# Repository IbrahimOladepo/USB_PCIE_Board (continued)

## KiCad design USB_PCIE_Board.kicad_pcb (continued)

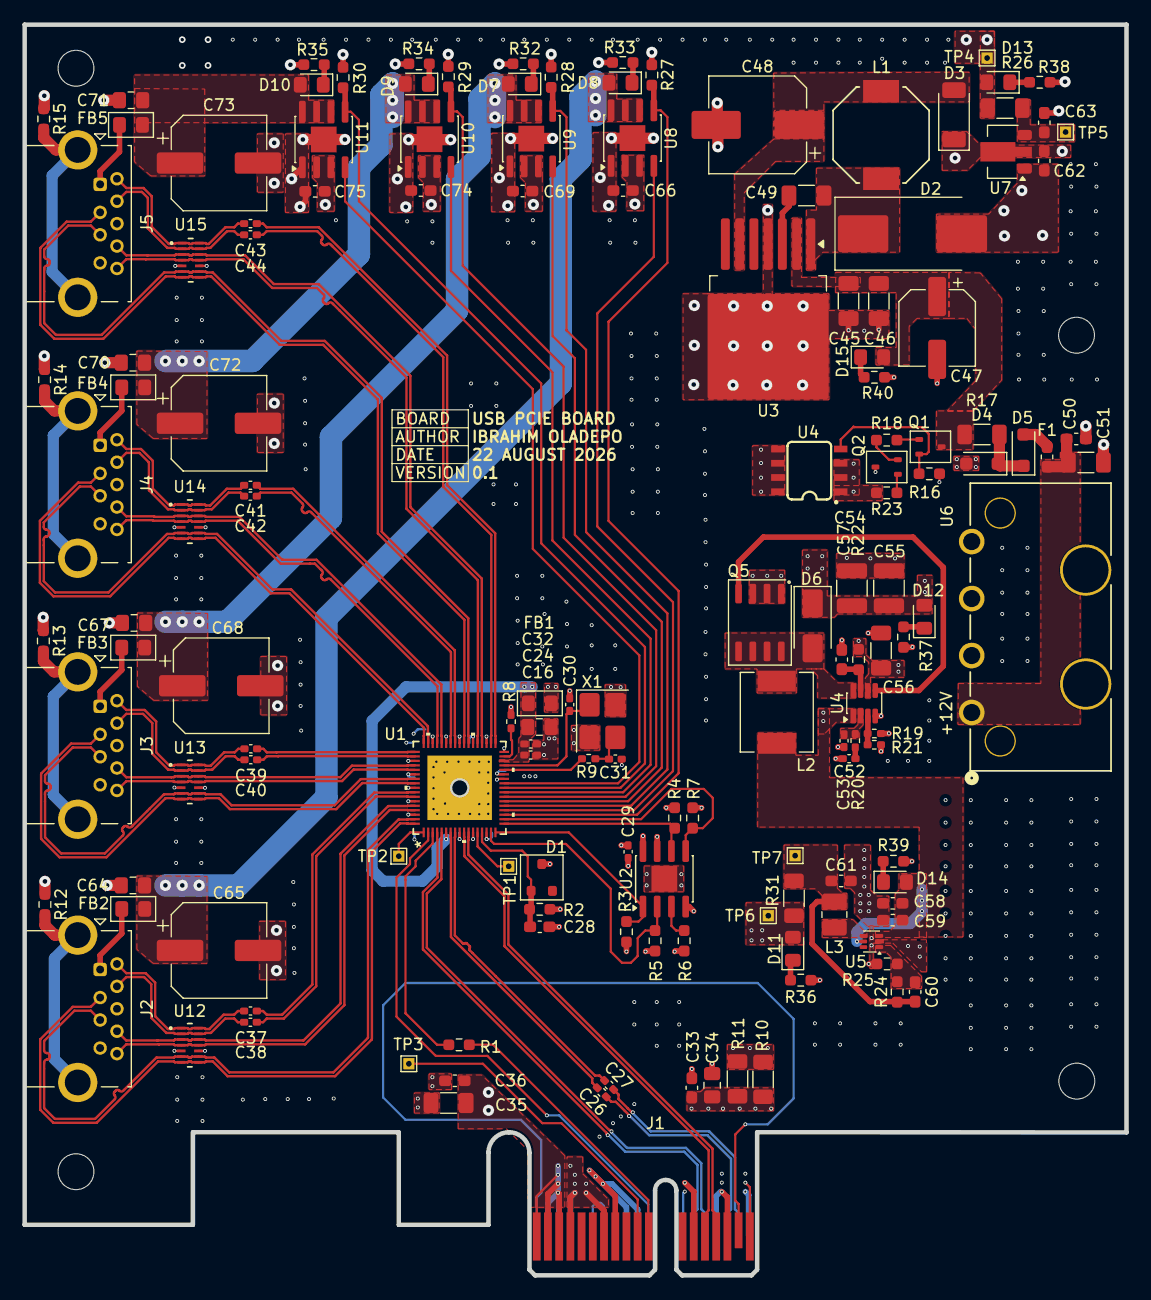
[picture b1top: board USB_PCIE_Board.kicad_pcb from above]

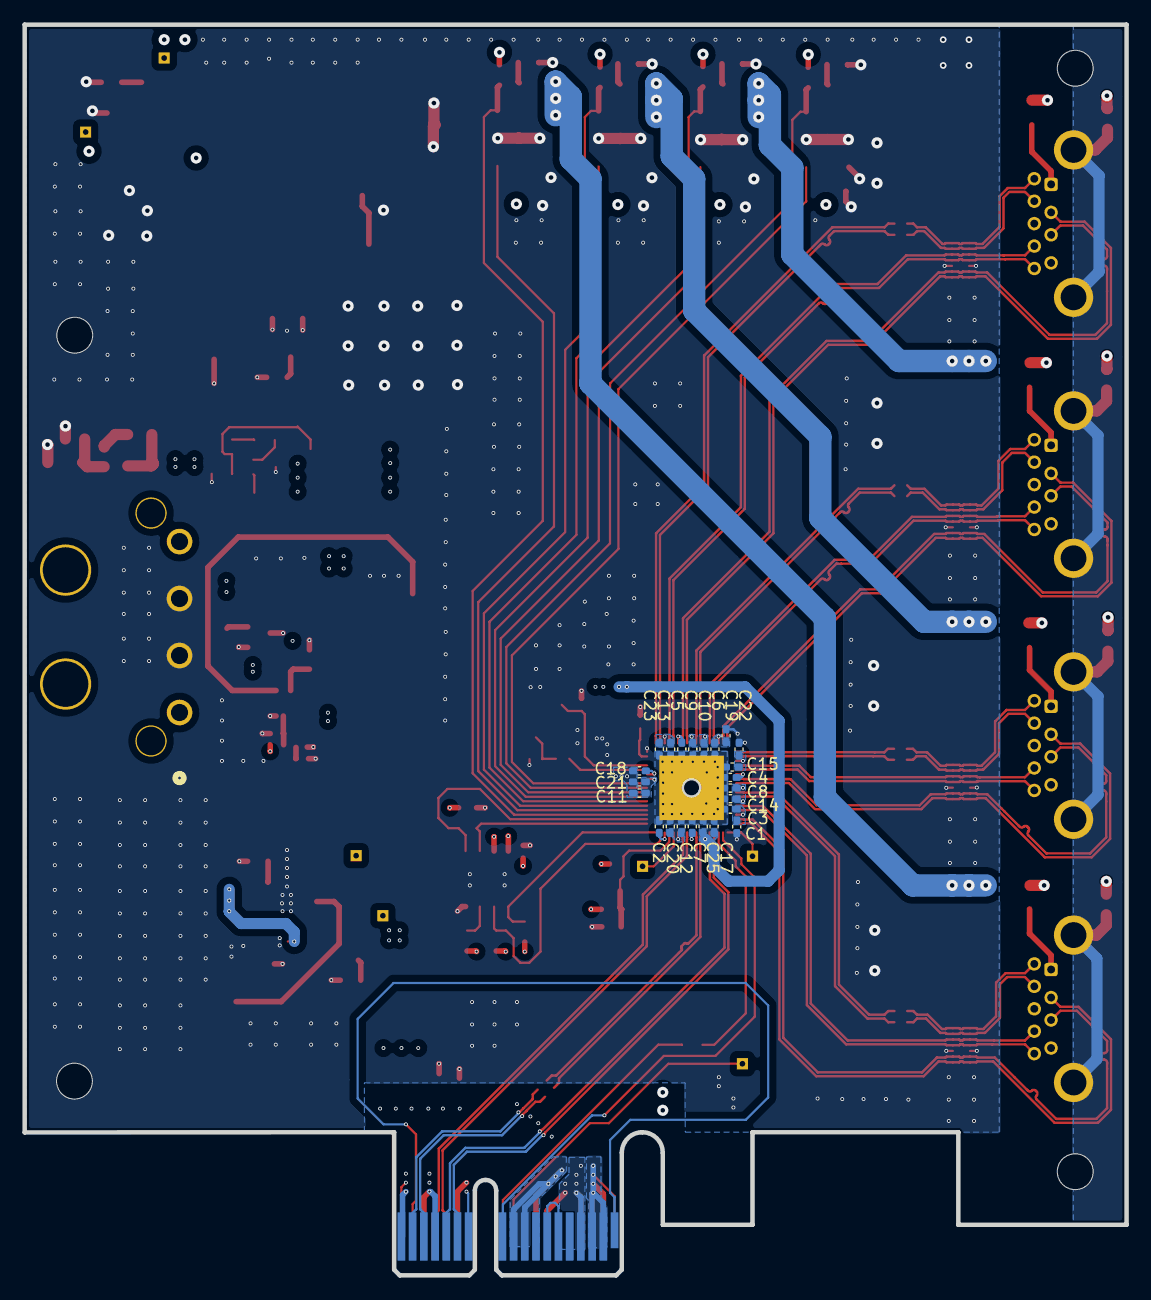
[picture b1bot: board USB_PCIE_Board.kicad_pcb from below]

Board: 4 copper layers, 98.2 x 111.5 mm, 175 parts (23 on the bottom side), 114 nets.

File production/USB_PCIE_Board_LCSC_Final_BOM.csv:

LCSC Part Number,Manufacture Part Number,Manufacturer,Customer NO.,Package,Description,RoHS,Quantity,Unit Price($),Ext.Price($),Estimated lead time (business days),Updated lead time,Date Code / Lot No.
C14663,CC0603KRX7R9BB104,YAGEO,"C33,C36,C50,C57,C59",0603,100nF ±10% 50V Ceramic Capacitor X7R 0603,YES,50,0.0151,0.76,,,
C60474,CC0402KRX7R7BB104,YAGEO,"C18,C19,C20,C21,C22,C23,C24,C25,C26,C27,C29,C37,C38,C39,C40,C41,",0402,100nF ±10% 16V Ceramic Capacitor X7R 0402,YES,100,0.0054,0.54,,,
C18305,BLM21PG600SN1D,muRata,"FB1,FB2,FB3,FB4,FB5",0805,60Ω@100MHz 1 Line Ferrite Bead 0805 3.5A 20mΩ,YES,20,0.0402,0.80,,,
C1972746,SF-0603S315-2,BOURNS,F1,0603,3.15A Surface Mount 0603,YES,2,0.5505,1.10,,,
C5588998,APTD2012LSYCK,Kingbright,"D14,D15",0805,Yellow 590nm LED Indication - Discrete 1.85V 0805,YES,5,0.2268,1.13,,,
C2837824,SMLMN2BCTT86C,ROHM,"D11,D12,D13",0805,Blue 476nm LED Indication - Discrete 2.9V 0805,YES,10,0.3083,3.08,,,
C2992528,SMLMN2WB1CW1,ROHM,"D7,D8,D9,D10",0805,White LED Indication - Discrete 2.9V 0805,YES,10,0.3253,3.25,,,
C110484,B320A-13-F,DIODES,D6,SMA(DO-214AC),1 Independent 20V 500mV@3A 3A SMA(DO-214AC) Single Diodes RoHS,YES,5,0.1615,0.81,,,
C2845139,RBR2MM30BTR,ROHM,"D4,D5",SOD-123FL,Diode Independent 30V 2A Surface Mount SOD-123FL,YES,5,0.1398,0.70,,,
C253526,RSX501LAM20TR,ROHM,D3,SOD-128,Diode 20V 5A Surface Mount SOD-128,YES,5,0.2183,1.09,,,
C85100,B560C-13-F,DIODES,D2,SMC(DO-214AB),1 Independent 60V 700mV@5A 5A SMC(DO-214AB) Single Diodes RoHS,YES,5,0.2117,1.06,,,
C261914,"1SS294,LF",TOSHIBA,D1,SC-59,Diode 40V 100mA Surface Mount SC-59,YES,10,0.0594,0.59,,,
C190722,16SVPC150M,PANASONIC,"C65,C68,C72,C73","SMD,D8xL6.9mm","150uF ±20% 16V Aluminum - Polymer Capacitors SMD,D8xL6.9mm 2000hrs@105℃",YES,8,1.1395,9.12,,,
C77042,GRM188R60J226MEA0D,muRata,"C58,C60,C61",0603,22uF ±20% 6.3V Ceramic Capacitor X5R 0603,YES,10,0.0572,0.57,,,
C60137,CC0402JRNPO9BN470,YAGEO,C53,0402,47pF ±5% 50V Ceramic Capacitor NP0 0402,YES,100,0.0028,0.28,,,
C23742,CL32A107MPVNNNE,Samsung Electro-Mechanics,"C54,C55",1210,100uF ±20% 10V Ceramic Capacitor X5R 1210,YES,4,0.5051,2.02,,,
C108081,RC1206JR-070RL,YAGEO,"R10,R11,R17,R26,R31",1206,0Ω 250mW 200V Thick Film Resistor ±5% 1206 Chip Resistor - Surface Mount RoHS,YES,50,0.0114,0.57,,,
C60133,CC0402KRX7R9BB103,YAGEO,"C1,C2,C3,C4,C5,C6,C7,C8,C9,C10,C11,C12,C13,C14,C15,C16,C17",0402,10nF ±10% 50V Ceramic Capacitor X7R 0402,YES,100,0.0056,0.56,,,
C29936,CL10B105KA8NNNC,Samsung Electro-Mechanics,"C28,C62,C63,C66,C69,C74,C75",0603,1uF ±10% 25V Ceramic Capacitor X7R 0603,YES,20,0.0216,0.43,,,
C2191663,GJM1555C1H8R0DB01D,muRata,"C30,C31",0402,8pF C0G 50V 0402 Ceramic Capacitors RoHS,YES,50,0.0207,1.04,,,
C326595,CC0805KKX7R7BB106,YAGEO,"C32,C34,C64,C67,C70,C71",0805,10uF ±10% 16V Ceramic Capacitor X7R 0805,YES,15,0.2428,3.64,,,
C162437,GRM319R61E106KA12D,muRata,"C35,C51,C56",1206,10uF ±10% 25V Ceramic Capacitor X5R 1206,YES,10,0.239,2.39,,,
C342646,C3216X7R1V685KT000E,TDK,"C45,C46",1206,6.8uF ±10% 35V Ceramic Capacitor X7R 1206,YES,4,0.5643,2.26,,,
C128458,EEEFK1H220P,PANASONIC,C47,"SMD,D6.3xL5.8mm",22uF ±20% 50V Aluminum Electrolytic Capacitors 2000hrs@105℃,YES,5,0.1618,0.81,,,
C494858,EEEFN1H181UP,PANASONIC,C48,"SMD,D8xL10.2mm",180uF ±20% 50V Aluminum Electrolytic Capacitors 2000hrs@105℃,YES,2,0.787,1.57,,,
C106239,CC1206KRX7R9BB103,YAGEO,C49,1206,10nF ±10% 50V Ceramic Capacitor X7R 1206,YES,20,0.0371,0.74,,,
C107024,CC0402KRX7R9BB182,YAGEO,C52,0402,1.8nF ±10% 50V Ceramic Capacitor X7R 0402,YES,100,0.01,1.00,,,
C2076772,CRCW040234K8FKED,VISHAY,R21,0402,34.8kΩ 62.5mW 50V Thick Film Resistor ±1% ±100ppm/℃ 0402 Chip Resistor - Surface Mount RoHS,YES,100,0.0032,0.32,,,
C844922,CRCW06031M00FKEA,VISHAY,R22,0603,100mW 1MΩ 75V Thick Film Resistor ±1% ±100ppm/℃ 0603 Chip Resistor - Surface Mount RoHS,YES,100,0.0049,0.49,,,
C2076703,CRCW0603133RFKEA,VISHAY,R25,0603,133Ω 100mW 75V Thick Film Resistor ±1% ±100ppm/℃ 0603 Chip Resistor - Surface Mount RoHS,YES,50,0.0084,0.42,,,
C22548,RC0603FR-071KL,YAGEO,"R32,R33,R34,R35,R36,R37,R38,R39",0603,100mW 1kΩ 75V Thick Film Resistor ±100ppm/℃ ±1% 0603 Chip Resistor - Surface Mount RoHS,YES,100,0.0052,0.52,,,
C56001,MX25L4006EM1I-12G,MXIC,U2,SOP-8,FLASH - NOR Memory IC 4Mbit SPI 86MHz SOP-8,YES,2,1.0759,2.15,,,
C527397,LM22678TJ-5.0/NOPB,TI,U3,TO-263-7,500kHz Step-down type Fixed 5V 5A TO-263-7 Voltage Regulators - DC DC Switching Regulators RoHS,YES,2,4.9834,9.97,,,
C459876,LTC3872ETS8#TRPBF,ADI,U4,TSOT-23-8,1 Adjustable Boost TSOT-23-8 DC DC Switching Controllers RoHS,YES,2,6.2227,12.45,,,
C5896722,RT5762CHGH6F,RICHTEK,U5,SOT-563,1.2MHz Step-down type Adjustable 2A 600mV~6V SOT-563 Voltage Regulators - DC DC Switching Regulators RoHS,YES,5,0.3323,1.66,,,
C706976,X5050WR-04S-N2SN,XKB Connection,U6,"Through Hole,Right Angle,P=5.08mm",Connector Header 4 position 5.08mm Pitch 10A Right Angle,YES,5,0.2296,1.15,,,
C460367,AP7215-33YG-13,DIODES,U7,SOT-89-3,"3.3V Positive Fixed SOT-89-3 Voltage Regulators - Linear, Low Drop Out (LDO) Regulators RoHS",YES,2,0.2497,0.50,,,
C2150698,AP2191SG-13,DIODES,"U8,U9,U10,U11",SOP-8,"1 Active High 1.5A High Side Switch SOP-8 Power Distribution Switches, Load Drivers RoHS",YES,10,0.1132,1.13,,,
C207281,SP3011-06UTG,Littelfuse,"U12,U13,U14,U15",UDFN-14(1.4x3.5),12.5VC Clamp 3A@8/20us Ipp ESD DIODE UDFN-14(1.4x3.5),YES,8,0.5242,4.19,,,
C87572,SPM6530T-1R0M120,TDK,L2,"SMD,7.1x6.5mm","13A 1uH ±20% 14.1A 7.81mΩ SMD,7.1x6.5mm Fixed Inductors RoHS",YES,5,0.1767,0.88,,,
C466222,TCC0402C0G100J500AT,CCTC,"C30,C31",0402,10pF ±5% 50V Ceramic Capacitor C0G 0402,YES,50,0.0034,0.17,,,
C255919,X1E0000210202,EPSON,X1,SMD3225-4P,Crystal 24MHz ±10ppm 9pF 40Ω SMD3225-4P,YES,5,0.2546,1.27,,,
C517755,TC0250B1742TCC,UNI-ROYAL,R20,0402,17.4kΩ ±0.1% 62.5mW 0402 Thin Film Resistor,YES,20,0.0225,0.45,,,
C1883521,AF0402FR-0711KL,YAGEO,R19,0402,62.5mW 11kΩ 50V Thick Film Resistor ±100ppm/℃ ±1% 0402 Chip Resistor - Surface Mount RoHS,YES,100,0.005,0.50,,,
C127447,RC0603JR-0747KL,YAGEO,R18,0603,47kΩ 100mW 75V Thick Film Resistor ±100ppm/℃ ±5% 0603 Chip Resistor - Surface Mount RoHS,YES,100,0.0049,0.49,,,
C413078,ERJ2RKF6800X,PANASONIC,R9,0402,100mW 680Ω Thick Film Resistor ±100ppm/℃ ±1% 0402 Chip Resistor - Surface Mount RoHS,YES,100,0.0043,0.43,,,
C413085,ERJ2RKF1601X,PANASONIC,R8,0402,100mW 1.6kΩ Thick Film Resistor ±100ppm/℃ ±1% 0402 Chip Resistor - Surface Mount RoHS,YES,100,0.0048,0.48,,,
C14675,RC0603FR-07100KL,YAGEO,"R4,R24",0603,100mW 100kΩ 75V Thick Film Resistor ±100ppm/℃ ±1% 0603 Chip Resistor - Surface Mount RoHS,YES,100,0.0047,0.47,,,
C159891,RK73B1JTTD103J,KOA,"R2,R3,R5,R6,R7,R16,R23,R27,R28,R29,R30,R40",0603,100mW 10kΩ 75V Thick Film Resistor ±5% ±200ppm/℃ 0603 Chip Resistor - Surface Mount RoHS,YES,100,0.004,0.40,,,
C95177,RC0603JR-070RL,YAGEO,"R1,R12,R13,R14,R15",0603,100mW 0Ω 75V Thick Film Resistor ±5% 0603 Chip Resistor - Surface Mount RoHS,YES,100,0.0034,0.34,,,
C142600,SI4134DY-T1-GE3,VISHAY,Q5,SO-8,N-Channel 30V 14A 5W Surface Mount SO-8,YES,5,0.2764,1.38,,,
C151586,DMT6016LSS-13,DIODES,Q4,SO-8,N-Channel 60V 9.2A 2.1W Surface Mount SO-8,YES,2,0.7893,1.58,,,
C111700,2SC4081T106R,ROHM,Q2,SC-70(SOT-323),Bipolar (BJT) Transistor NPN 50V 150mA 180MHz 200mW Surface Mount SC-70(SOT-323),YES,20,0.0412,0.82,,,
C111698,2SA1576AT106R,ROHM,Q1,SC-70(SOT-323),Bipolar (BJT) Transistor PNP 50V 150mA 140MHz 200mW Surface Mount SC-70(SOT-323),YES,20,0.0291,0.58,,,
C909806,DFE252012F-1R5M=P2,muRata,L3,1008,2.7A 1.5uH ±20% 58mΩ 3.8A 1008 Fixed Inductors RoHS,YES,5,0.142,0.71,,,
C2045037,SRU8043-3R9Y,BOURNS,L1,"SMD,8x8mm","4.8A 3.9uH ±30% 14.6mΩ 4A Magnetic Shielded Inductor SMD,8x8mm Fixed Inductors RoHS",YES,2,1.201,2.40,,,
C6376748,484050001,MOLEX,"J2,J3,J4,J5",Through Hole,"Through Hole USB, DVI, HDMI Connector Assemblies RoHS",YES,6,3.1262,18.76,,,
C355375,UPD720201K8-701-BAC-A,RENESAS,,QFN-68-EP(8x8),"USB to PCI Express 4 5Gbps QFN-68-EP(8x8) Controllers ",NO,5,3.0081,15.04,2026-09-07,,26+
